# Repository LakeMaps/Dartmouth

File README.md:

# PCB
This is where the PCBs go, because "boat" was taken

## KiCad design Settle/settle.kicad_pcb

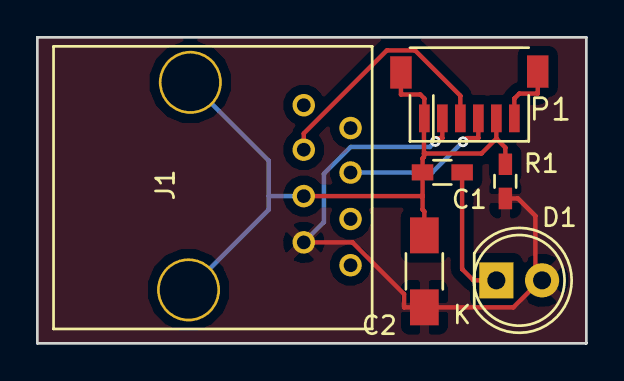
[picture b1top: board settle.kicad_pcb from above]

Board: 2 copper layers, 30.5 x 17.0 mm, 6 parts (0 on the bottom side), 5 nets.

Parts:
C1: 0.1u; C_0603_HandSoldering
C2: 10u; C_1206_HandSoldering
D1: LED; LED-5MM
J1: RJ45; RJ45_Header
P1: CONN_01X06; JST-6
R1: 150; R_0603_HandSoldering

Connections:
+5V: C1.1, C2.1, D1.2, J1.2, P1.2
/Rx: J1.6, P1.3
/Tx: J1.5, P1.4
Earth: C1.2, C2.2, J1.4, J1.9, P1.1, P1.5, R1.2
unnamed: D1.1, R1.1

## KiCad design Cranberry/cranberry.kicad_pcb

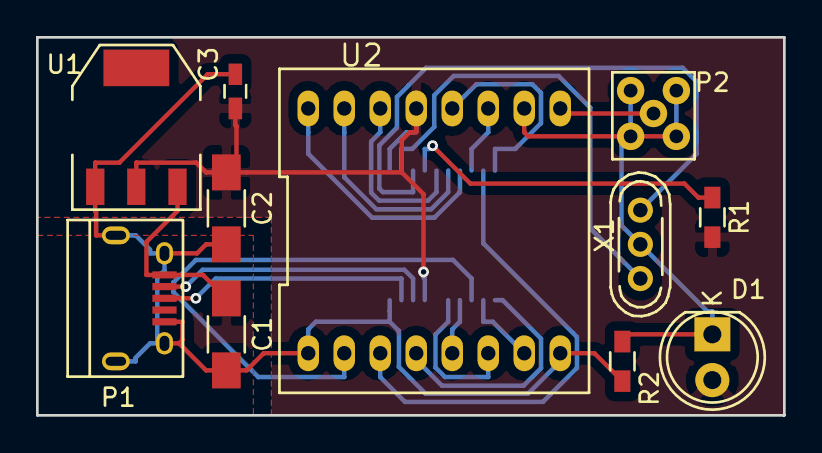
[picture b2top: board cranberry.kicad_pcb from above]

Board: 2 copper layers, 41.5 x 21.0 mm, 12 parts (1 on the bottom side), 21 nets.

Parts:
C1, C2: 4.7u; C_1206_HandSoldering
C3: 10n; C_0603_HandSoldering
D1: LED; LED-5MM
P1: USB_OTG; USB_Micro-B
P2: SMA; RP-SMA
R1: 390; R_0603_HandSoldering
R2: 33; R_0603_HandSoldering
U1: NCP1117ST33T3G; SOT-223
U2: RFM69HCW; RFM_Module
U3: MCP2210; SSOP-20_5.3x7.2mm_Pitch0.65mm
X1: 12MHz; Crystal_HC52-U_Vertical_3Pin

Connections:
+3V3: C2.1, C3.1, D1.2, R1.1, U1.2, U2.13, U3.1, U3.17
+5V: C1.1, P1.1, U1.3
/IO0: U2.14, U3.5
/IO1: U2.15, U3.6
/IO2: U2.16, U3.7
/IO3: U2.11, U3.8
/IO4: U2.12, U3.10
/IO5: U2.7, U3.12
/MISO: U2.2, U3.13
/MOSI: U2.3, U3.9
/RFM_RST: U2.6, U3.15
/SCK: U2.4, U3.11
/SS_0: U2.5, U3.14
/USB_D+: P1.3, U3.19
/USB_D-: P1.2, U3.18
Earth: C1.2, C2.2, C3.2, P1.5, P1.6, P2.2, R2.2, U1.1, U2.1, U2.8, U2.10, U3.20, X1.3
unnamed: D1.1, R2.1
unnamed: P2.1, U2.9
unnamed: R1.2, U3.4
unnamed: U3.2, X1.1
unnamed: U3.3, X1.2

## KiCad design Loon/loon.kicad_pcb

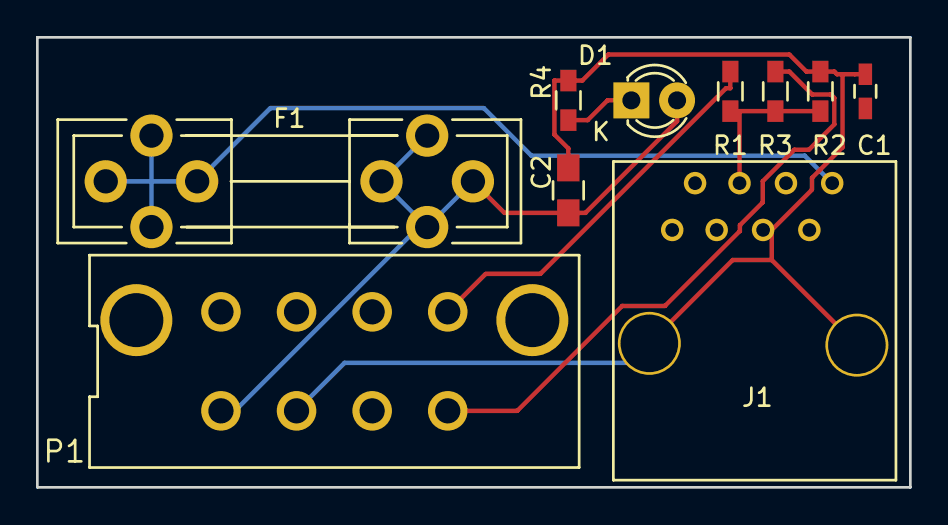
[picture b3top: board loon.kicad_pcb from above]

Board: 2 copper layers, 48.5 x 25.0 mm, 10 parts (0 on the bottom side), 7 nets.

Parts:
C1: 0.1u; C_0603_HandSoldering
C2: 10u; C_0805_HandSoldering
D1: LED; LED-3MM
F1: FUSE; Fuseholder5x20_horiz_open_universal_Type-III
J1: RJ45; RJ45_Header
P1: CONN_01X07; 8_Pin_Minifit
R1, R2, R3: R; R_0603_HandSoldering
R4: 1k; R_0603_HandSoldering

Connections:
+12V: F1.2, J1.1
/12_fuse: C2.1, D1.2, F1.1, P1.1
/Tx: J1.5, R1.1, R2.2, R3.1
Earth: C1.2, C2.2, J1.4, J1.9, P1.2, R3.2, R4.2
unnamed: D1.1, R4.1
unnamed: P1.4, R2.1
unnamed: P1.5, R1.2

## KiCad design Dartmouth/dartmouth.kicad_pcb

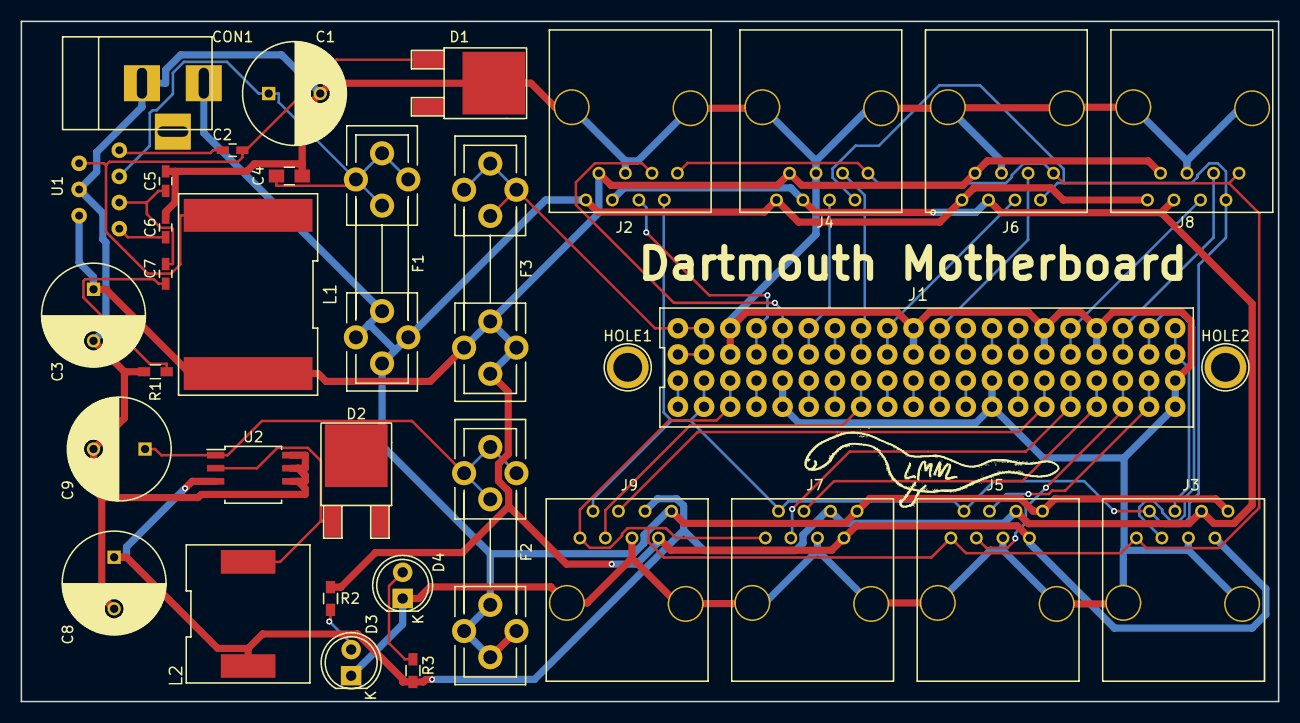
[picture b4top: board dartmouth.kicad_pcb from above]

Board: 2 copper layers, 122.0 x 66.0 mm, 36 parts (0 on the bottom side), 33 nets.

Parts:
C1: 2200uF; C_Radial_D10_L13_P5
C2, C6: 0.22uF; C_0603_HandSoldering
C3: 470uF; C_Radial_D10_L13_P5
C4: 4.7uF; C_0805_HandSoldering
C5: 680pF; C_0603_HandSoldering
C7: 1200pF; C_0603_HandSoldering
C8, C9: 470u; C_Radial_D10_L13_P5
CON1: BARREL_JACK
D1, D2: STPS1045B-TR; TO-252-2Lead
D3, D4: LED; LED-5MM
F1, F2, F3: FUSE; Fuseholder5x20_horiz_open_universal_Type-III
HOLE1, HOLE2: 1pin
J1: RPi_GPIO; Raspi_Header
J2, J3, J4, J5, J6, J7, J8, J9: RJ45; RJ45_Header
L1: 56uH; SRP_Series_Ind
L2: 47uH; SRR1210A_Series_Ind
LOGO: GrandyHype_25mm
R1: 39k; R_0603_HandSoldering
R2: 220; R_0603_HandSoldering
R3: 33; R_0603_HandSoldering
U1: SI-8050Y; TO-220-7
U2: AP1509; SOIJ-8_5.3x5.3mm_Pitch1.27mm

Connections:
+3V3: C8.1, J2.3, J3.3, J4.3, J5.3, J6.3, J7.3, J8.3, J9.3, L2.1, R3.1, U2.3
+5V: C3.1, F3.1, J2.2, J3.2, J4.2, J5.2, J6.2, J7.2, J8.2, J9.2, L1.2, R2.1, U1.6
+12V: CON1.1, F1.1, F2.1, J2.1, J3.1, J4.1, J5.1, J6.1, J7.1, J8.1, J9.1
/5VPi: F3.2, J1.2, J1.4
/12-3v3Fused: C9.1, F2.2, U2.1
/12-5Fuse: C1.1, C4.1, F1.2, U1.3
/GPIO05: J1.29, J9.5
/GPIO06: J1.31, J7.6
/GPIO12: J1.32, J8.5
/GPIO13: J1.33, J7.5
/GPIO14: J1.8, J2.5
/GPIO15: J1.10, J2.6
/GPIO16: J1.36, J8.6
/GPIO18: J1.12, J4.5
/GPIO19: J1.35, J5.6
/GPIO20: J1.38, J3.6
/GPIO21: J1.40, J3.5
/GPIO22: J1.15, J9.6
/GPIO23: J1.16, J4.6
/GPIO24: J1.18, J6.5
/GPIO25: J1.22, J6.6
/GPIO26: J1.37, J5.5
/SCL: J1.5, J2.8, J3.8, J4.8, J5.8, J6.8, J7.8, J8.8, J9.8
/SDA: J1.3, J2.7, J3.7, J4.7, J5.7, J6.7, J7.7, J8.7, J9.7
Earth: C1.2, C3.2, C4.2, C5.2, C6.2, C8.2, C9.2, CON1.2, D1.2, D3.1, D4.1, J1.6, J1.9, J1.20, J1.25, J1.30, J1.34, J1.39, J2.4, J2.9, J3.4, J3.9, J4.4, J4.9, J5.4, J5.9, J6.4, J6.9, J7.4, J7.9, J8.4, J8.9, J9.4, J9.9, R1.2, U1.4, U2.4, U2.5, U2.6, U2.7, U2.8
unnamed: C2.1, U1.1
unnamed: C2.2, D1.1, L1.1, U1.2
unnamed: C5.1, C7.1, U1.5
unnamed: C6.1, U1.7
unnamed: C7.2, R1.1
unnamed: D2.1, L2.2, U2.2
unnamed: D3.2, R2.2
unnamed: D4.2, R3.2

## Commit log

2016-07-27 Initial commit of project files
2016-07-27 Changed board names
    Motherboard is now, and will always be "dartmouth", the nuturing mother
    who brought me into this world
2016-07-31 Intitial commit of Cranberry
2016-08-01 Added custom MCP2210, Ceramic Resonator, and RFM69 to custom library
2016-10-25 Updated to working copy
